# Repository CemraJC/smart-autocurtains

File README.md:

# Smart Auto-curtain System

A foundational system for controlling a stepper motor based on remote input,
ambient light readings and locally measured temperature.

Every curtain system is different, so some independent design is required.

**Please read this whole document before building! Seriously!** (I mean, c'mon,
it's not that long - it'll save you a bunch of time in the setup)

## What it does

The basic system will open or close curtains based on remote control input. In
the event of remote control failure, the system has two integrated buttons to
operate the curtains.

**However,** the system can do much more than simple remote operation. If
"Auto-brightness control" is enabled, the system will close the blinds if
outside light levels exceed a pre-determined threshold. This is to assist with
sleeping in bright-early environments.

Also, depending on the local temperature (and your currently active settings),
the system may open the blinds to allow sunlight or air circulation.

Note that the system does not use the local time to operate, because the
hardware required adds unnecessary complexity to the setup and user operation of
the system.

## System components:

1. Arduino Nano
    * Could be substituted for a different type of Arduino
    * Minimum specs:
    * Must have a regulated power supply
2. Stepper Motor and controller (more info - todo)
3. 5V power supply and cable (more info - check max rating for stepper)
4. 2 momentary push buttons
5. 1 photoresistor
6. 1 temperature sensor
7. 1 IR LED (for receiving remote signals)
8. 1 RGB LED (or 3 separate red, green, blue LEDs - diffused!)
9. Arbitrary IR remote (buttons will be programmed in)
10. Perforated circuit board (minimum 300x250)
11. Solid-core wire (cleaner than stranded)
12. Resistors (220, 1k, 10k)
13. Cardboard / MDF (more info when final casing completed)
14. Bump-press limit switch (for homing the system)

## Tools required:

1. Soldering Iron and Small Fan (to evacuate soldering smoke)
2. Wire strippers (optional, but highly recommended)
3. Screwdriver

## Building (TODO)

# Set-up procedure

The Smart Autocurtains require the following setup:

* Set the remote buttons
* Set the "away" position

These settings are saved in the Arduino's non-volatile memory, so the settings
are not wiped in a loss-of-power event. In other words, you should only have
to set up the system once.

Before attempting setup, make sure that the power is on. The system should
flash a green LED once when the power is turned on. Then, the curtains will
automatically seek the home position. If it is the first run, a red LED should
turn on next.

## Setting remote buttons

When you first run the system (or run it after a user-reset), you will need to
record the buttons on your remote. Every remote is different, however this
should still be a simple procedure. If you have difficulties, try changing the
remote you are using and making sure the remote is functional.

To check that your remote has battery, point a smartphone camera at the IR LED
on the front. Then, press a button. If the camera shows a flash, then the
remote is functional.

Some remotes are more reliable than others. Hold the remote a least 2 feet
(0.5 meters) away from the IR receiver and press each button quickly.

To record which buttons do what, follow these steps:

1. Observe that a red LED is lit up on the device (first run only)
1. Press the button on the remote that you want to correspond to "open"
1. Keep pressing this button (it needs four consecutive signals). If the LED flashes Red/Blue (Purple) then the remote sent a partial signal and you need to start again. Make sure that each press is quick.
1. Observe that the system flashes a blue LED exactly once
1. Choose and press the "close" button on the remote (4 times again)
1. Observe that the system flashes a blue LED exactly twice
1. Choose and press the "cancel" button (same deal as with the others)
1. Observe that the system flashes a blue LED exactly three times
1. Choose and press the "auto-dawn" button (to enable/disable closing the curtains when it gets bright in the morning)
1. Observe that the system flashes a blue LED exactly four times
1. Choose and press the "auto-temp" button (to enable/disable force-opening the curtains when the temperature exceeds 28 degrees C)
1. Observe that the system flashes a blue LED exactly five times and the curtains proceed to the home position

Note that it will take about 30 seconds for the settings to be saved into the
permanent memory, so don't power down the system at least until then.

**Important:** on first run, be prepared to quickly power down the system in
the event that the homing switch does not function correctly. If the stepper
is allowed to run past home, it may stall and/or cause damage to the device or
your curtains.

Now is a good time to mention that we take no responsibility for any damages
caused by the system (although, to be fair, it's pretty unlikely that anything
seriously bad could happen).

## Setting home and away positions

#### What are home and away positions?

The curtains have two key positions, "home" and "away". The home position is
set by where the homing switch is placed. Depending on how the system is set
up, home and away could be in very different places. Regardless, home is the
position the curtains should be in when _open_. Home is set automatically by
the system, assuming the limit switch is properly in place.

Once home is found (the system re-homes every time on startup), the "away"
position must be set by the user (if it has not been already). 

#### How to set the away position

To set the away position, wait for the "red blue" LED sequence (purple on an
RGB system) and then proceed to press and hold the open/close buttons (on the
remote, or the onboard buttons) to set the away position. If the directions
are wrong (i.e the open button closes the curtains) then you will need to
switch the rails to which the curtains are clipped.

_Note:_ Holding down a button may not work on some remotes. In this case, you
will need to repeatedly press the open/close remote buttons to step the
curtains into the desired position. Alternatively, press and hold the onboard
system buttons (this should always work).

Once you are happy with the curtain's position as the "away" position, press
and hold both onboard buttons for 2 seconds. The away position is now set, it
should not need to be set again (unless you reset the system).

## All done!

When the away position is set successfully, the device should flash a green
LED. Your Smart Autocurtains are now ready for use!

# How to use the Smart Autocurtains

Once the curtains are set up according to the above procedure, you can operate
the curtains in the following ways:

## Using the remote

With a single press of the open or close buttons, the curtains will travel the
full distance to the home/away position respectively. If you only want the
curtains, say half-open, then press the cancel button halfway through the
motion.

Once a motion is canceled, a subsequent motion will pick back up from where
the curtains currently are.

Note that, since this system is designed to be flexible, remote performance is
not always as good as if it was a native system.

## Using the on-board buttons

There are two buttons, one to open, and one to close. If both buttons are
pressed at once, the curtains will cancel their current motion (assuming there
is one being made).

**WARNING:** When you first press a button, the system needs time to wake up
from low power mode. Because of this, you may need to hold one of the buttons
for at most 1 second to get the system to respond. The system will re-enter
low power mode after 10 seconds of no user input.

If both buttons are pressed and held for 4 seconds, the entire system should
reset - including clearing all settings, remote buttons and positions. The
system will need to be setup from scratch if reset in this way.

## With the "smart" features

There are two smart features, "autodawn control" and "autotemp control". These
smart features operate the curtains without user input in response to readings
from light and temperature sensors.

To **enable/disable** these features individually, press the corresponding buttons
on the remote that were recorded during setup and observe that the system
should flash a red or green LED for "off" or "on" respectively.

## Autodawn

This feature is the reason this system exists. Where I (the developer) live,
it gets fairly bright at around 4 or 5am. I prefer to wake up at 7am, but the sun
won't let me. You get the idea.

The system uses a light sensor to determine if it is currently night. It does
this by waiting for the light levels to drop below a "night-time" threshold
for a minimum of 30 minutes. If it is night (or the system _thinks_ it is),
then the curtains will open, to allow air circulation.

Then, when light levels exceed the "night-time" threshold level for at least
30 minutes, the system will close the blinds to prevent early-brightness from
waking you up.

## Autotemp

Having the curtains closed for brightness is only good as long as the
temperature is bearable. Based on external research, 28 degrees C is a general
threshold at which humans find it difficult to sleep. For this reason, if
autotemp is enabled, the curtains will be forced to open to allow air
circulation - regardless of autodawn. Of course, user input will override the
auto-temp setting (for up to 1 hour) unless autotemp is disabled, and then re-
enabled.

Whether or not this feature makes sense for you depends on your unique
circumstance. It also assumes that your windows are actually open - otherwise,
all it does is let in sunlight and make things worse!

# Common Issues

## I have to hold the on-board button before it works

This is normal. When you first press a button, the system needs time to wake
up from low power mode. Because of this, you may need to hold one of the
buttons for at most 1 second to get the system to respond. The system will re-
enter low power mode after 10 seconds of no user input.

## My remote doesn't work when I try to set it up

Try another remote. The system should recognize most remotes, but there are a
few whacky ones out there that don't work for some reason. If you can't get a
_normal_ Infra-Red TV remote to work, and you've tried other remotes, then you
may need to reset the system.

## My remote doesn't work anymore - it used to!

To check that your remote has battery, point a smartphone camera at the IR LED
on the front. Then, press a button that you have recorded on the system. If
the camera shows a flash, then the remote is functional.

If your remote is working, but the system is not responding, then try holding
the remote really close to the IR receiver on the device, shielding if from
the environment with your hand. If this fixes the problem, you will need to
identify possible sources of infra-red interference and remove them from the
environment.

If the system still doesn't work, follow the troubleshooting procedure below
to cycle the power, and if necessary, reset the entire system.

## I have some other problem

Follow the troubleshooting procedure below. If this still does not resolve
your issue, then I'm out of ideas. If you find a problem that is not resolved
by following the procedure below, don't hesitate to open a GitHub Issue and I
will try to work with you to resolve the problem.

# Troubleshooting

## Deep cycle the power

If the system is malfunctioning, follow these steps to try and resolve the issue:

1. Turn the system off with the power switch, then turn off the switch at the wall.
2. Wait for 5 seconds to ensure all power has drained from the system
3. Turn the wall switch back on (nothing should be happening yet)
4. Turn the device's power switch back on

Now, you should see the system flash a green LED twice and the system should
go to home.

## Well, that didn't fix it.

Press and hold the onboard buttons for 4 seconds. The system should flash a
red LED twice, then reset itself - clearing all settings. Then, go through the
setup procedure again and see if the system is now functioning correctly.

You should not have to do this often/at all. If you find yourself regularly
doing this, then check that the stepper is rotating _continuously_ (i.e. no
jumpiness or skips) when opening/closing the curtains. If it does not rotate
continuously, then you will need to reduce the torque on the stepper by either
adjusting the curtains, so they move with less friction, or by upgrading the
stepper motor to one with higher torque. A stepper upgrade is difficult work,
and is left as an exercise only to advanced users. 

## Something is probably broken.

If there are no green flashes on startup, confirm that the LEDs are functional.
Still no flashes, then either there is something wrong with the code, or the
Arduino is malfunctioning - possibly due to loose connections, or a short
circuit. If you have made modifications to the code, you will need to debug it
yourself.

If you do see two green flashes, the system should move the curtains
to the home position. If the curtains do not move, and are not already at the
home position, check the wiring to the stepper motor and confirm that power is
being correctly applied.

If the wiring is correct, and still no motion, use your fingers to test the
temperature of the motor and all the IC's (integrated circuit chips). They
should all be at room temperature, or only slightly warm. If any of the chips
are too hot to touch, immediately power down the system and triple check the
wiring, paying careful attention to potential short circuits due to faulty
resistors/capacitors.

If the curtains move, but do not stop when they reach home (or they home too
early/at random positions) power down the system and confirm that the limit
switch is functioning correctly and is properly hooked up to the Arduino.

If the curtains do not reliably return to the home and away positions, go to
the previous section to check that the stepper is functioning correctly.

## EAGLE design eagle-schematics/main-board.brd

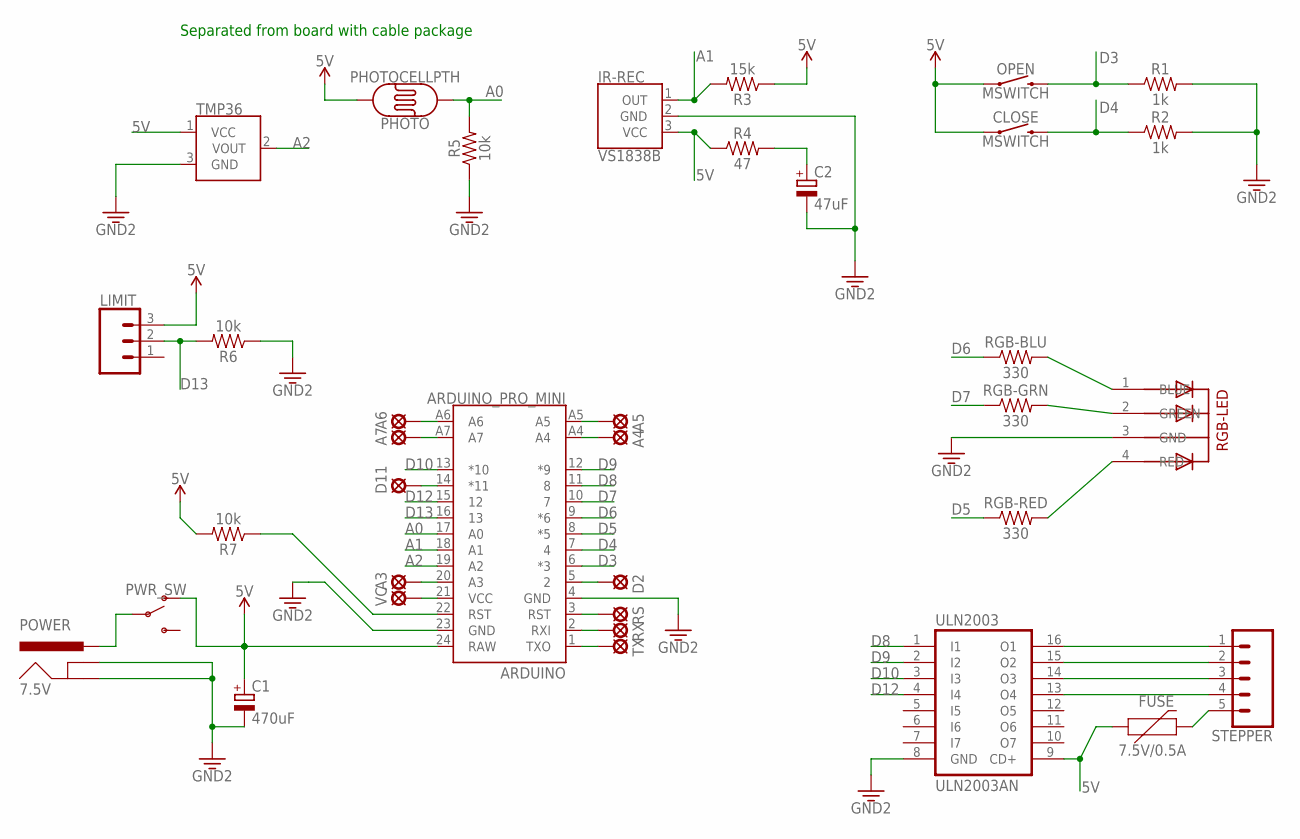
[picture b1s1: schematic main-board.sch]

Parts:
7.5V: POWER; POWER_JACK_SLOT
A3, A4, A5, A6, A7: LSP11
ARDUINO: ARDUINO_PRO_MINI
C1: 470uF; B45181A
C2: 47uF; B45181A
CLOSE: MSWITCH; TACTILE_SWITCH_PTH_6.0MM
D2, D11: LSP11
FUSE: 7.5V/0.5A; PTH
IR-REC: VS1838B; BRM-2508_VERT
LIMIT: CONN_03; 1X03
OPEN: MSWITCH; TACTILE_SWITCH_PTH_6.0MM
PHOTO: PHOTOCELLPTH; PHOTOCELL
PWR_SW: SWITCH-SPDT-PTH-11.6X4.0MM; SWITCH_SPDT_PTH_11.6X4.0MM
R1, R2: 1k; AXIAL-0.3
R3: 15k; AXIAL-0.3
R4: 47; AXIAL-0.3
R5, R6, R7: 10k; AXIAL-0.3
RGB-BLU: 330; AXIAL-0.3
RGB-GRN: 330; AXIAL-0.3
RGB-LED: DIFFUSE; LED5MMRGB
RGB-RED: 330; AXIAL-0.3
RS: LSP11
RX: LSP11
STEPPER: CONN_05; 1X05
TMP36: TMP36GT9; TO-92
TX: LSP11
ULN2003: ULN2003AN; DIL16
VC: LSP11

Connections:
5V: ARDUINO.24 (RAW), C1.+, CLOSE.1, FUSE.P$1 (1), IR-REC.3 (VCC), LIMIT.3, OPEN.1, PHOTO.2, PWR_SW.1 (O), R3.P$1 (1), R4.P$1 (1), R7.P$2 (2), TMP36.1 (VCC), ULN2003.9 (CD+)
A0: ARDUINO.17 (A0), PHOTO.1, R5.P$2 (2)
A1: ARDUINO.18 (A1), IR-REC.1 (OUT), R3.P$2 (2)
A2: ARDUINO.19 (A2), TMP36.2 (VOUT)
AFTER: ARDUINO.22 (RST), R7.P$1 (1)
D3: ARDUINO.6 (*3), OPEN.3 (2), R1.P$1 (1)
D4: ARDUINO.7 (4), CLOSE.3 (2), R2.P$1 (1)
D5: ARDUINO.8 (*5), RGB-RED.P$1 (1)
D6: ARDUINO.9 (*6), RGB-BLU.P$1 (1)
D7: ARDUINO.10 (7), RGB-GRN.P$1 (1)
D8: ARDUINO.11 (8), ULN2003.1 (I1)
D9: ARDUINO.12 (*9), ULN2003.2 (I2)
D10: ARDUINO.13 (*10), ULN2003.3 (I3)
D12: ARDUINO.15 (12), ULN2003.4 (I4)
D13: ARDUINO.16 (13), LIMIT.2, R6.P$2 (2)
FUSE: FUSE.P$2 (2), STEPPER.5
GND: 7.5V.GND@1 (GNDBREAK), 7.5V.GND@2 (GND), ARDUINO.4 (GND), ARDUINO.23 (GND), C1.-, C2.-, IR-REC.2 (GND), R1.P$2 (2), R2.P$2 (2), R5.P$1 (1), R6.P$1 (1), RGB-LED.3 (GND), TMP36.3 (GND), ULN2003.8 (GND)
unnamed: 7.5V.PWR, PWR_SW.2
unnamed: C2.+, R4.P$2 (2)
unnamed: RGB-BLU.P$2 (2), RGB-LED.1 (BLUE)
unnamed: RGB-GRN.P$2 (2), RGB-LED.2 (GREEN)
unnamed: STEPPER.1, ULN2003.16 (O1)
unnamed: STEPPER.2, ULN2003.15 (O2)
unnamed: STEPPER.3, ULN2003.14 (O3)
unnamed: STEPPER.4, ULN2003.13 (O4)
unnamed: RGB-LED.4 (RED), RGB-RED.P$2 (2)
unnamed: A6.MP, ARDUINO.A6
unnamed: A7.MP, ARDUINO.A7
unnamed: A5.MP, ARDUINO.A5
unnamed: A4.MP, ARDUINO.A4
unnamed: A3.MP, ARDUINO.20 (A3)
unnamed: ARDUINO.21 (VCC), VC.MP
unnamed: ARDUINO.5 (2), D2.MP
unnamed: ARDUINO.3 (RST), RS.MP
unnamed: ARDUINO.2 (RXI), RX.MP
unnamed: ARDUINO.1 (TXO), TX.MP
unnamed: ARDUINO.14 (*11), D11.MP

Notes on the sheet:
Separated from board with cable package

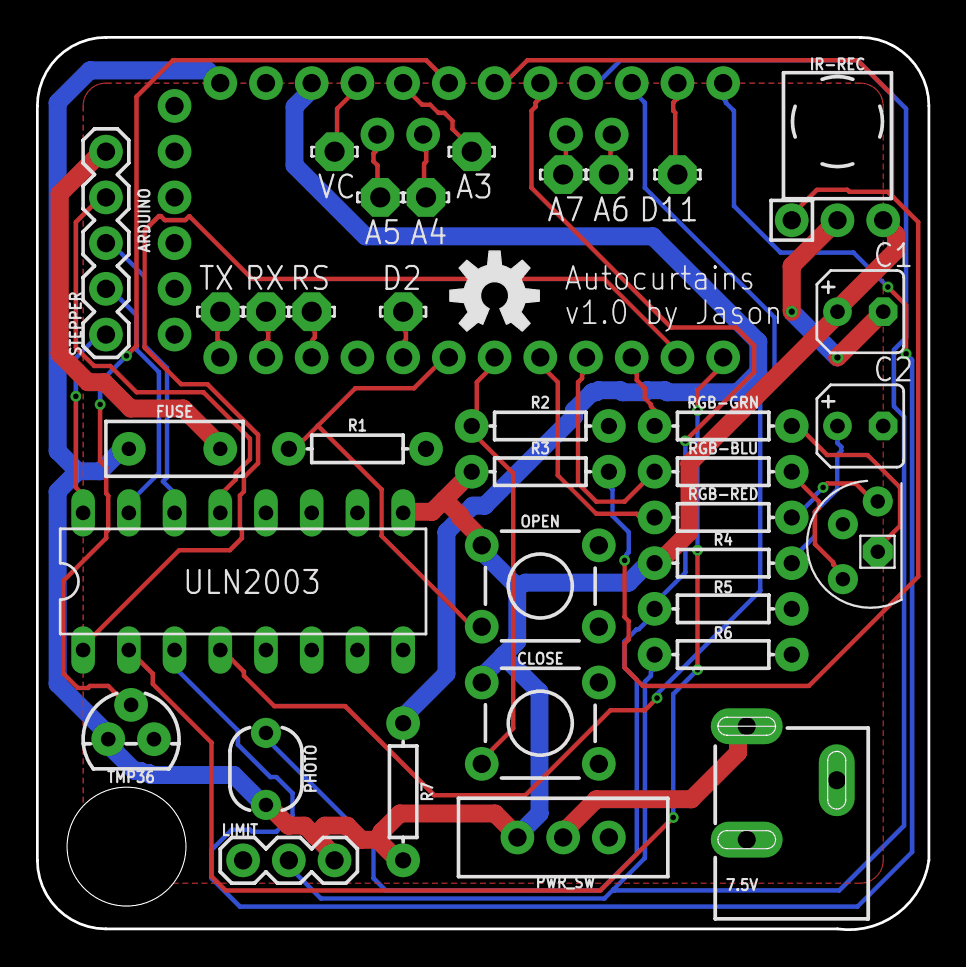
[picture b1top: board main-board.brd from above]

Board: 2 copper layers, 49.5 x 49.6 mm, 37 parts (0 on the bottom side), 37 nets.

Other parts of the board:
U$1: OSHW-LOGO-M

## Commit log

2017-12-02 Stepper experiment complete
2017-12-03 Continuing work on EEPROM integration
2017-12-03 Started EAGLE project
2017-12-04 README and RGB LED stuff
2017-12-04 Finished RGBDisplay Project Library
2017-12-04 Added state hooks to RGBDisplay
2017-12-05 Updates to RGBDisplay
2017-12-05 Started IR Remote input routines
2017-12-05 Finished input control section for remote control
2017-12-06 Added Sensors to InputControl
2017-12-06 Updated Schematic and BOM
2017-12-06 Started work on CurtainControl
2017-12-07 Completed phase 1 of work on stepper library
2017-12-07 Implemented Homing Routine
2017-12-09 Working on Remote Reliability
2017-12-09 Started work on tying components together
2017-12-10 Finishing up hooking it together
2017-12-10 Added documentation
2017-12-10 Fixed remote reliability issue with main loop
2017-12-10 Commenced testing of all the features (and RGB output control)
2017-12-10 Finished testing autodawn functions
2017-12-19 Added EAGLE files
2017-12-19 Updated BOM
2017-12-19 Added images of PCB
2017-12-19 Added Gerber files (CAM Job)
2017-12-20 Updated PCB design

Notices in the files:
parts and their libraries:
SparkFun-Switches: Licensing: Creative Commons ShareAlike 4.0 International - https://creativecommons.org/licenses/by-sa/4.0
